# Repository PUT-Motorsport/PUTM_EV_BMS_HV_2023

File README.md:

# PUTM_EV_BMS_HV_MASTER_2023
Accumulator Managment System (High Voltage Battery Managment System)

## Overview
The AMS system consists of two main parts, the master and multiple slaves.

The apparatus is responsible for the managment of the battery as a whole, determining it's states like: state of charge or unsafe state plausibility. It also supervises the turning on and off of the hv bus.

## Master
The AMS Master is the center of the whole system it's responsible for most of the tasks: current measurement, high voltage relay control, slave control, high voltage measurement and communication with the car. 

### Software
The AMS system havely relies on RTOS (Real Time Operating System) for seperating and managing different tasks. The system is divided mainly into three parts:
- main task - responsible for control over the whole system,
- subsidiary tasks - for off handling time consuming calculations or interfacing,
- communication tasks - for handling communication with external systems like CAN communication with the car or isoSPI for communication with the slaves.

### Hardware 
The AMS is powered by STM32G484xx, a powerful, new gen MCU capable of handling varius communication interfaces and tasks. On board there are also three 24bit ADC ICs responsible for taking precise measurments of flowing current and voltage present on HV bus. For interfacing with other components the AMS uses M80 and M300 series Harwin connectors which offer high reliability. The board also features other logic components all on a custom 4 layer board.

### The research and development work was carried out was a part of the Student Scientific Clubs Create Innovations (SKNTI) program. [Ministry of Science and Higher Education](https://www.gov.pl/web/nauka)

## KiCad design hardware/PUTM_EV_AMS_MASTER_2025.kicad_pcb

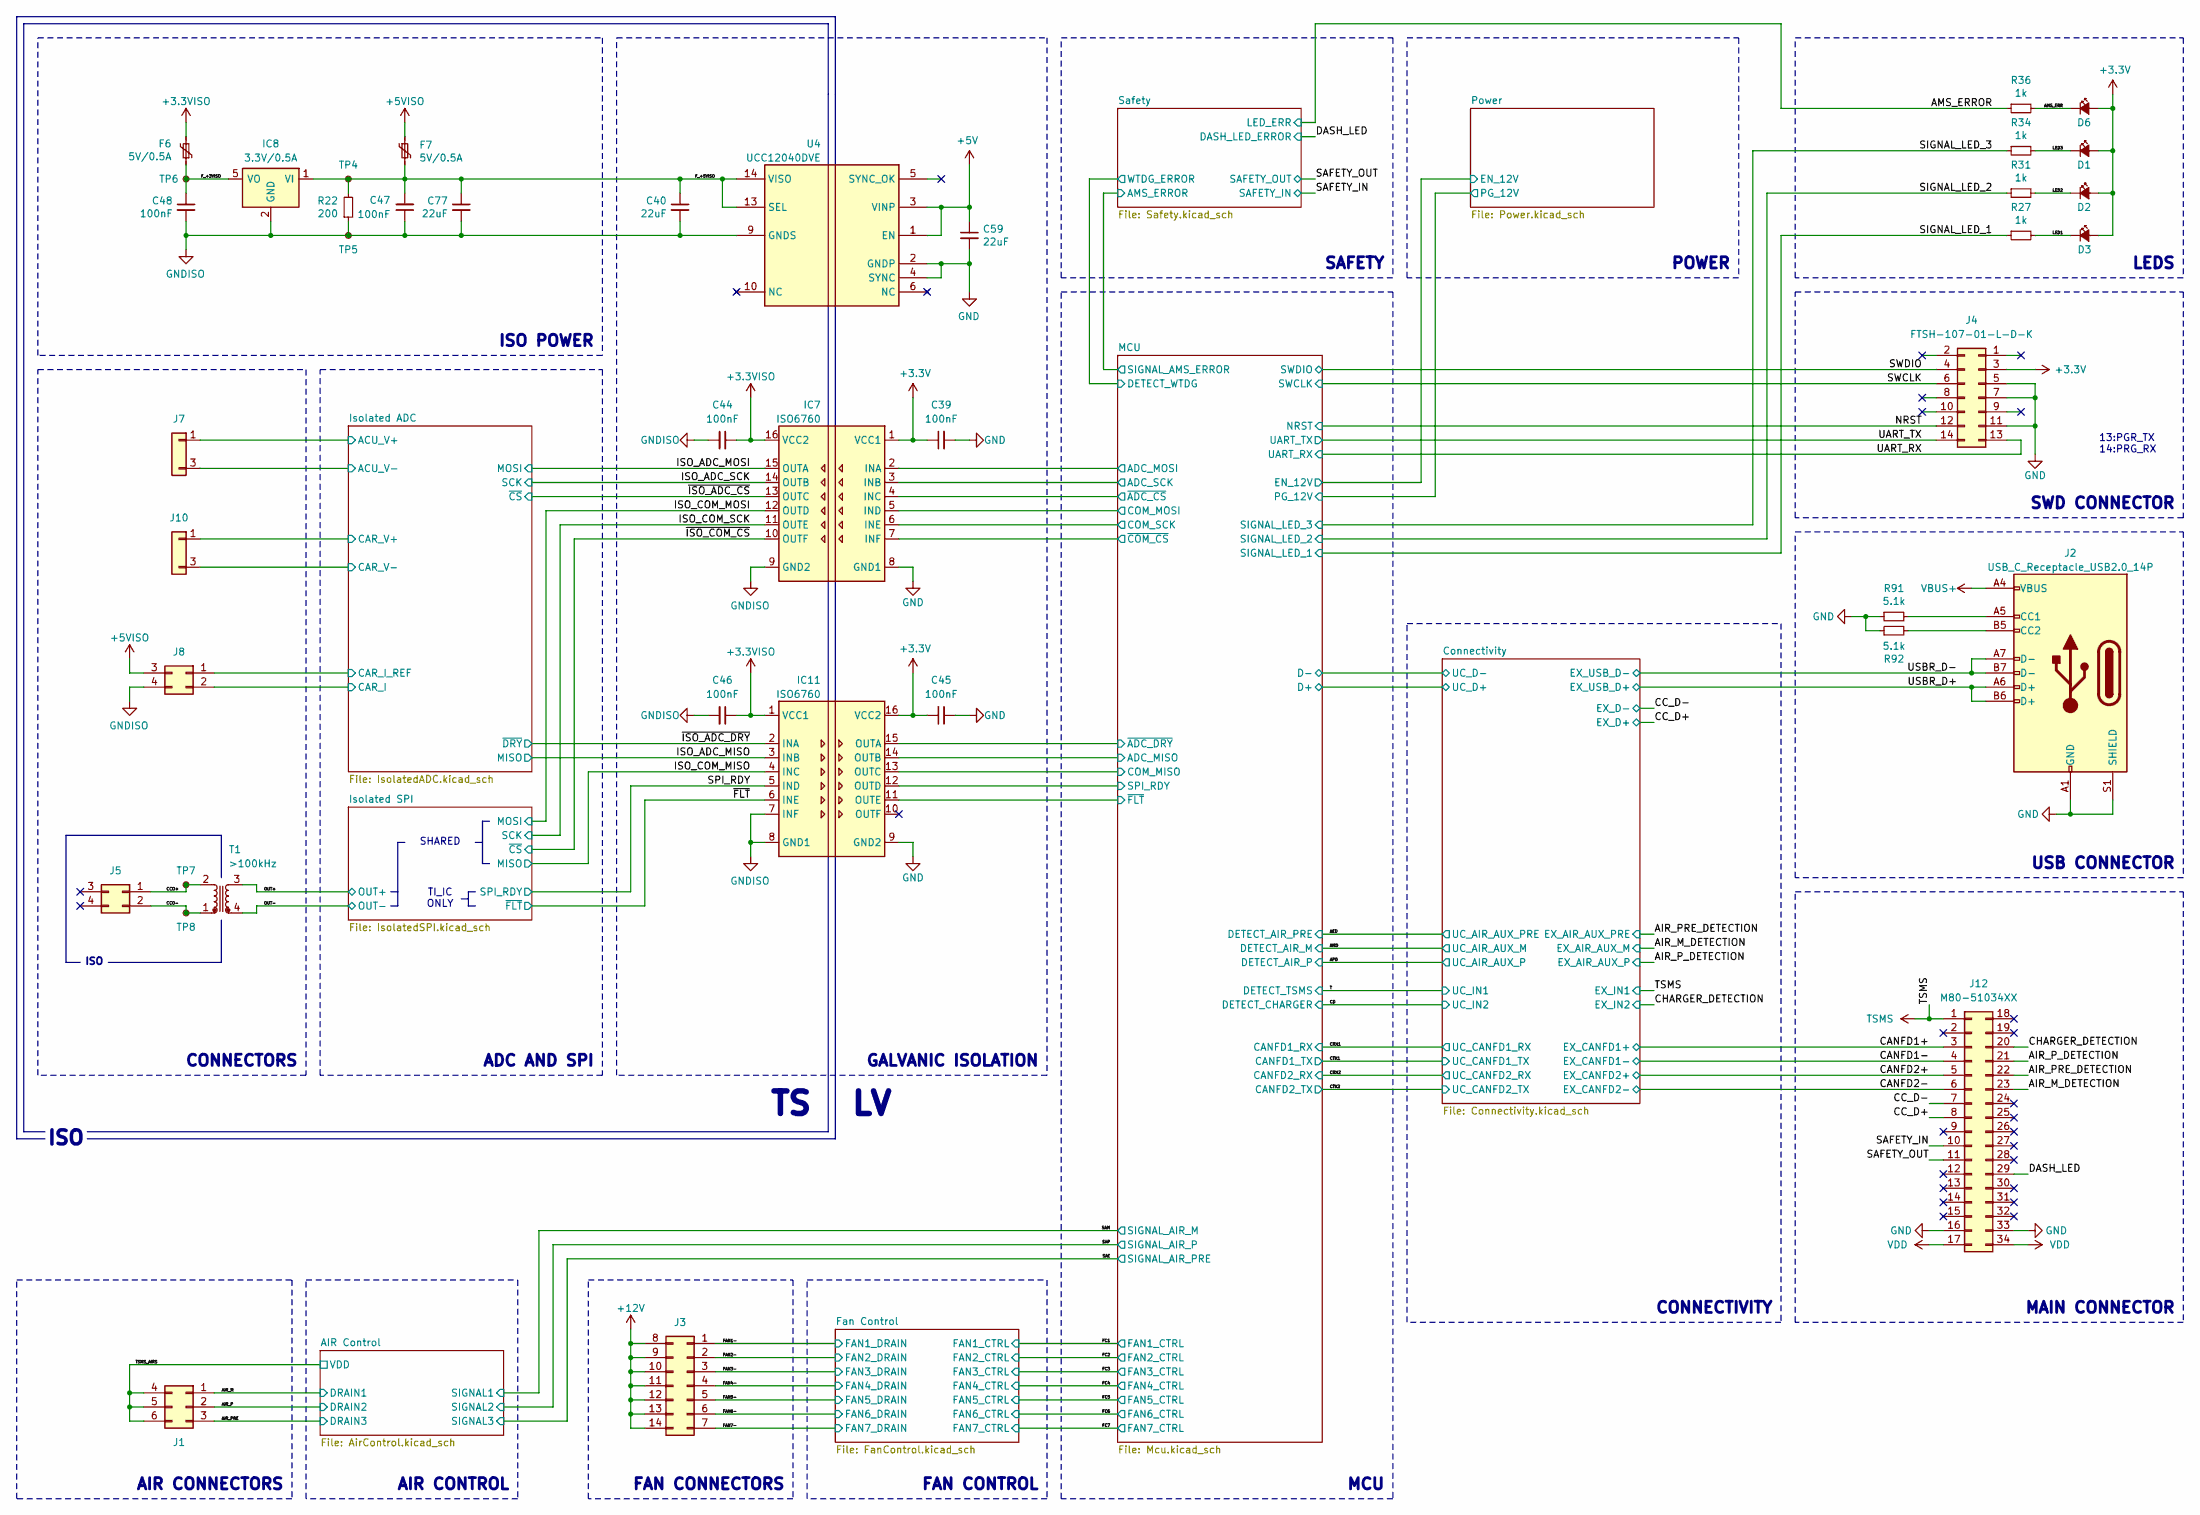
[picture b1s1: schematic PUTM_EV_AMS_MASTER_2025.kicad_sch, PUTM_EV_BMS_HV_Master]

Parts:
C39, C44, C45, C46, C47, C48: 100nF; C_0603_1608Metric; Manufacturer_Part_Number --
C40, C59, C77: 22uF; C_0805_2012Metric; Manufacturer_Part_Number --
D1, D2, D3, D6: SML-D12U1WT86; LED_0603_1608Metric; Manufacturer_Part_Number --
F6, F7: 5V/0.5A; Fuse_0805_2012Metric; Manufacturer_Part_Number 0ZCH0050FF2G; Mouser Part Number 530-0ZCH0050FF2G
IC7, IC11: ISO6760; SOIC-16W_7.5x10.3mm_P1.27mm; Mouser Part Number 595-ISO6760QDWRQ1
IC8: 3.3V/0.5A; SOT-23-5; Mouser Part Number 595-TPS7B92033DBVR
J1: M80-5100642; M80-51006YY; Mouser Part Number 855-M80-5100642
J2: USB_C_Receptacle_USB2.0_14P; USB_C_Receptacle_JAE_DX07S024WJ3R400
J3: M80-51014XX; M80-51014YY; Mouser Part Number 855-M80-5101422
J4: FTSH-107-01-L-D-K; FTSH-107-XX-YYY-D-K; Mouser Part Number 200-FTSH10701LDK
J5, J8: M80-51004XX; M80-51004YY; Mouser Part Number 855-M80-5100442
J7, J10: M300-MV10345M1; M300MV10345M1; Mouser Part Number 855-M300-MV10345M1
J12: M80-51034XX; M80-51034YY; Mouser Part Number 855-M80-5103442
R22: 200; R_0603_1608Metric; Manufacturer_Part_Number --
R27, R31, R34, R36: 1k; R_0603_1608Metric; Manufacturer_Part_Number --
R91, R92: 5.1k; R_0603_1608Metric; Manufacturer_Part_Number --
T1: >100kHz; SOP254P914X350-4N; Mouser Part Number 851-ESMIT-4180/C
TP4, TP5, TP6, TP7, TP8: TestPoint_Small; TestPoint_THTPad_D1.0mm_Drill0.5mm
U4: UCC12040DVE; SOIC-16W_7.5x10.3mm_P1.27mm; Mouser Part Number 595-UCC12040DVE

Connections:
+3.3V: C39.1, C45.1, D1.2 (A), D2.2 (A), D3.2 (A), D6.2 (A), IC7.1 (VCC1), IC11.16 (VCC2), J4.3; also elsewhere on the board
+3.3VISO: C44.1, C46.1, F6.2, IC7.16 (VCC2), IC11.1 (VCC1); also elsewhere on the board
+5V: C59.1, U4.1 (EN), U4.3 (VINP); also elsewhere on the board
+5VISO: F7.1, J8.3; also elsewhere on the board
+12V: J3.8, J3.9, J3.10, J3.11, J3.12, J3.13, J3.14; also elsewhere on the board
/AIR_M: J1.1; also elsewhere on the board
/AIR_M_DETECTION: J12.23; also elsewhere on the board
/AIR_P: J1.2; also elsewhere on the board
/AIR_PRE: J1.3; also elsewhere on the board
/AIR_PRE_DETECTION: J12.22; also elsewhere on the board
/AIR_P_DETECTION: J12.21; also elsewhere on the board
/AMS_ERR: D6.1 (K), R36.2
/AMS_ERROR: R36.1; also elsewhere on the board
/CANFD1+: J12.3; also elsewhere on the board
/CANFD1-: J12.4; also elsewhere on the board
/CANFD2+: J12.5; also elsewhere on the board
/CANFD2-: J12.6; also elsewhere on the board
/CCO+: J5.1, T1.2, TP7.1
/CCO-: J5.2, T1.1, TP8.1
/CC_D+: J12.8; also elsewhere on the board
/CC_D-: J12.7; also elsewhere on the board
/CHARGER_DETECTION: J12.20; also elsewhere on the board
/DASH_LED: J12.29; also elsewhere on the board
/FAN1-: J3.1; also elsewhere on the board
/FAN2-: J3.2; also elsewhere on the board
/FAN3-: J3.3; also elsewhere on the board
/FAN4-: J3.4; also elsewhere on the board
/FAN5-: J3.5; also elsewhere on the board
/FAN6-: J3.6; also elsewhere on the board
/FAN7-: J3.7; also elsewhere on the board
/F_+3VISO: C48.1, F6.1, IC8.5 (VO), TP6.1
/F_+5VISO: C40.1, C47.2, C77.1, F7.2, IC8.1 (VI), R22.2, TP4.1, U4.13 (SEL), U4.14 (VISO)
/ISO_ADC_MISO: IC11.3 (INB); also elsewhere on the board
/ISO_ADC_MOSI: IC7.15 (OUTA); also elsewhere on the board
/ISO_ADC_SCK: IC7.14 (OUTB); also elsewhere on the board
/ISO_COM_MISO: IC11.4 (INC); also elsewhere on the board
/ISO_COM_MOSI: IC7.12 (OUTD); also elsewhere on the board
/ISO_COM_SCK: IC7.11 (OUTE); also elsewhere on the board
/Isolated ADC/ACU_V+: J7.1; also elsewhere on the board
/Isolated ADC/ACU_V-: J7.3; also elsewhere on the board
/Isolated ADC/CAR_V+: J10.1; also elsewhere on the board
/Isolated ADC/CAR_V-: J10.3; also elsewhere on the board
/Isolated ADC/I+: J8.2; also elsewhere on the board
/Isolated ADC/I-: J8.1; also elsewhere on the board
/LED1: D3.1 (K), R27.2
/LED2: D2.1 (K), R31.2
/LED3: D1.1 (K), R34.2
/MCU/ADC_MISO: IC11.14 (OUTB); also elsewhere on the board
/MCU/ADC_MOSI: IC7.2 (INA); also elsewhere on the board
/MCU/ADC_SCK: IC7.3 (INB); also elsewhere on the board
/MCU/COM_MISO: IC11.13 (OUTC); also elsewhere on the board
/MCU/COM_MOSI: IC7.5 (IND); also elsewhere on the board
/MCU/COM_SCK: IC7.6 (INE); also elsewhere on the board
/MCU/SPI_RDY: IC11.12 (OUTD); also elsewhere on the board
/MCU/~ADC_CS: IC7.4 (INC); also elsewhere on the board
/MCU/~ADC_DRY: IC11.15 (OUTA); also elsewhere on the board
/MCU/~COM_CS: IC7.7 (INF); also elsewhere on the board
/MCU/~FLT: IC11.11 (OUTE); also elsewhere on the board
/NRST: J4.12; also elsewhere on the board
/OUT+: T1.3; also elsewhere on the board
/OUT-: T1.4; also elsewhere on the board
/SAFETY_IN: J12.10; also elsewhere on the board
/SAFETY_OUT: J12.11; also elsewhere on the board
/SIGNAL_LED_1: R27.1; also elsewhere on the board
/SIGNAL_LED_2: R31.1; also elsewhere on the board
/SIGNAL_LED_3: R34.1; also elsewhere on the board
/SPI_RDY: IC11.5 (IND); also elsewhere on the board
/SWCLK: J4.6; also elsewhere on the board
/SWDIO: J4.4; also elsewhere on the board
/TSMS_AIRS: J1.4, J1.5, J1.6; also elsewhere on the board
/UART_RX: J4.13; also elsewhere on the board
/UART_TX: J4.14; also elsewhere on the board
/USBR_D+: J2.A6 (D+), J2.B6 (D+); also elsewhere on the board
/USBR_D-: J2.A7 (D-), J2.B7 (D-); also elsewhere on the board
/~FLT: IC11.6 (INE); also elsewhere on the board
/~ISO_ADC_CS: IC7.13 (OUTC); also elsewhere on the board
/~ISO_ADC_DRY: IC11.2 (INA); also elsewhere on the board
/~ISO_COM_CS: IC7.10 (OUTF); also elsewhere on the board
GND: C39.2, C45.2, C59.2, IC7.8 (GND1), IC11.9 (GND2), J2.A1 (GND), J2.A12 (GND), J2.B1 (GND), J2.B12 (GND), J2.S1 (SHIELD), J4.5, J4.7, J4.11, J12.16, J12.33, R91.1, R92.1, U4.2 (GNDP), U4.4 (SYNC); also elsewhere on the board
GNDISO: C40.2, C44.2, C46.2, C47.1, C48.2, C77.2, IC7.9 (GND2), IC8.2 (GND), IC11.7 (INF), IC11.8 (GND1), J8.4, R22.1, TP5.1, U4.9 (GNDS), U4.15 (GNDS), U4.16 (GNDS); also elsewhere on the board
unnamed: J2.A5 (CC1), R91.2
unnamed: J2.B5 (CC2), R92.2
TSMS: J12.1; also elsewhere on the board
VBUS+: J2.A4 (VBUS), J2.A9 (VBUS), J2.B4 (VBUS), J2.B9 (VBUS); also elsewhere on the board
VDD: J12.17, J12.34; also elsewhere on the board

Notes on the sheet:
TI_IC ONLY
GALVANIC ISOLATION
FAN CONNECTORS
MAIN CONNECTOR
SAFETY
MCU
AIR CONNECTORS
SHARED
FAN CONTROL
LEDS
SWD CONNECTOR
USB CONNECTOR
13:PGR_TX 14:PRG_RX
ISO
AIR CONTROL
CONNECTORS
CONNECTIVITY
ISO POWER
POWER
ADC AND SPI

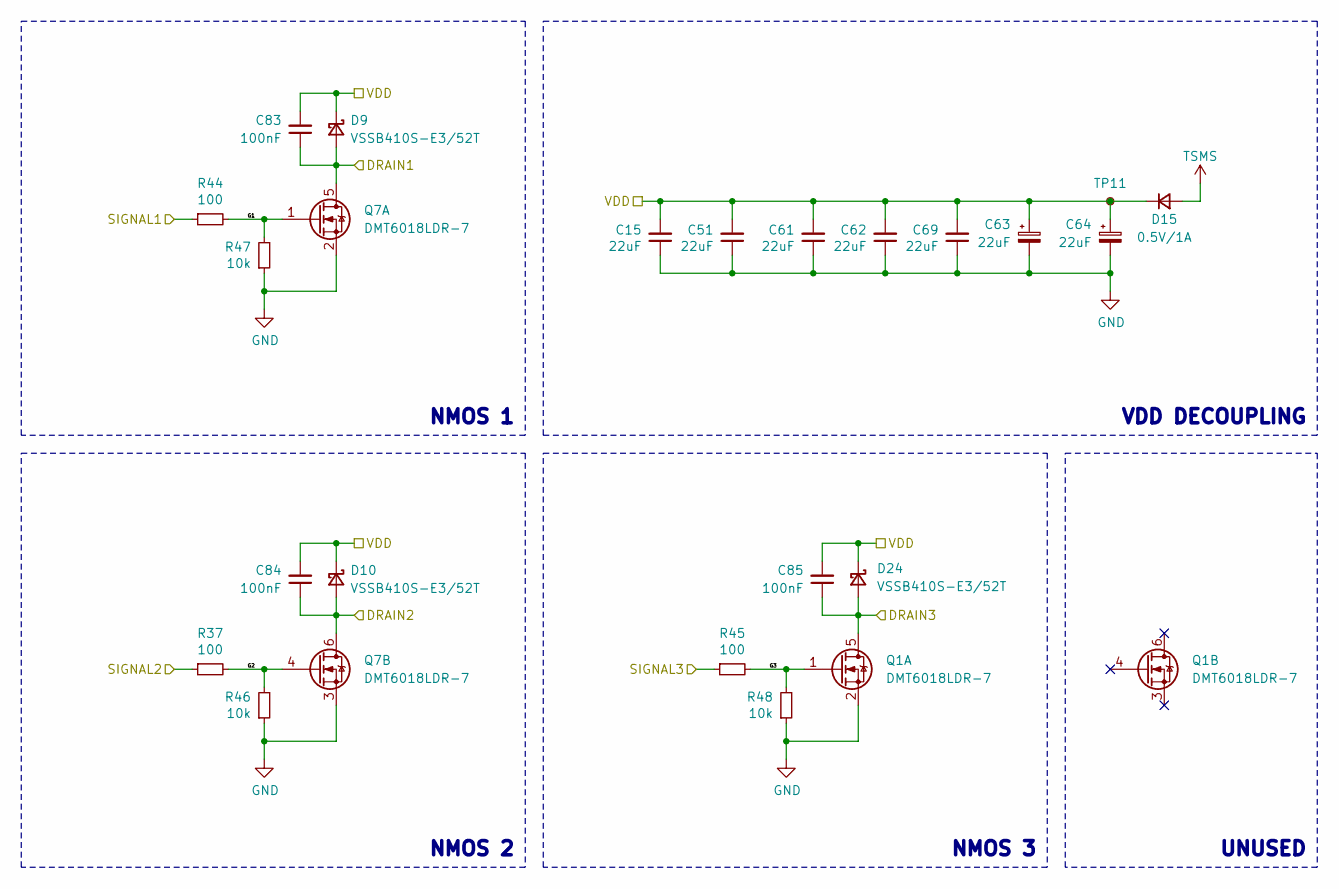
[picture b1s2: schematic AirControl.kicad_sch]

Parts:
C15, C51, C61, C62, C69: 22uF; C_0805_2012Metric; Manufacturer_Part_Number CL21A107MQYNNWE
C63, C64: 22uF; CP_Elec_4x5.8
C83, C84, C85: 100nF; C_0603_1608Metric; Manufacturer_Part_Number --
D9, D10, D24: VSSB410S-E3/52T; D_SOD-123; Manufacturer_Part_Number VSSB410S-E3/52T; Mouser Part Number 625-VSSB410S-E3/52T
D15: 0.5V/1A; D_SOD-123
Q1, Q7: DMT6018LDR-7; DMT6018LDR7; Mouser Part Number 621-DMT6018LDR-7
R37, R44, R45: 100; R_0603_1608Metric; Manufacturer_Part_Number --
R46, R47, R48: 10k; R_0603_1608Metric; Manufacturer_Part_Number --
TP11: TestPoint_Small; TestPoint_THTPad_D1.0mm_Drill0.5mm

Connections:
/AIR Control/G1: Q7.1 (G1), R44.2, R47.2
/AIR Control/G2: Q7.4 (G2), R37.2, R46.2
/AIR Control/G3: Q1.1 (G1), R45.2, R48.2
/AIR_M: C83.1, D9.2 (A), Q7.5 (D1); also elsewhere on the board
/AIR_P: C84.1, D10.2 (A), Q7.6 (D2); also elsewhere on the board
/AIR_PRE: C85.1, D24.2 (A), Q1.5 (D1); also elsewhere on the board
/SAE: R45.1; also elsewhere on the board
/SAM: R44.1; also elsewhere on the board
/SAP: R37.1; also elsewhere on the board
/TSMS_AIRS: C15.2, C51.2, C61.2, C62.2, C63.1, C64.1, C69.2, C83.2, C84.2, C85.2, D9.1 (K), D10.1 (K), D15.1 (K), D24.1 (K), TP11.1; also elsewhere on the board
GND: C15.1, C51.1, C61.1, C62.1, C63.2, C64.2, C69.1, Q1.2 (S1), Q7.2 (S1), Q7.3 (S2), R46.1, R47.1, R48.1; also elsewhere on the board
TSMS: D15.2 (A); also elsewhere on the board

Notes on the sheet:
UNUSED
NMOS 1
VDD DECOUPLING
NMOS 2
NMOS 3

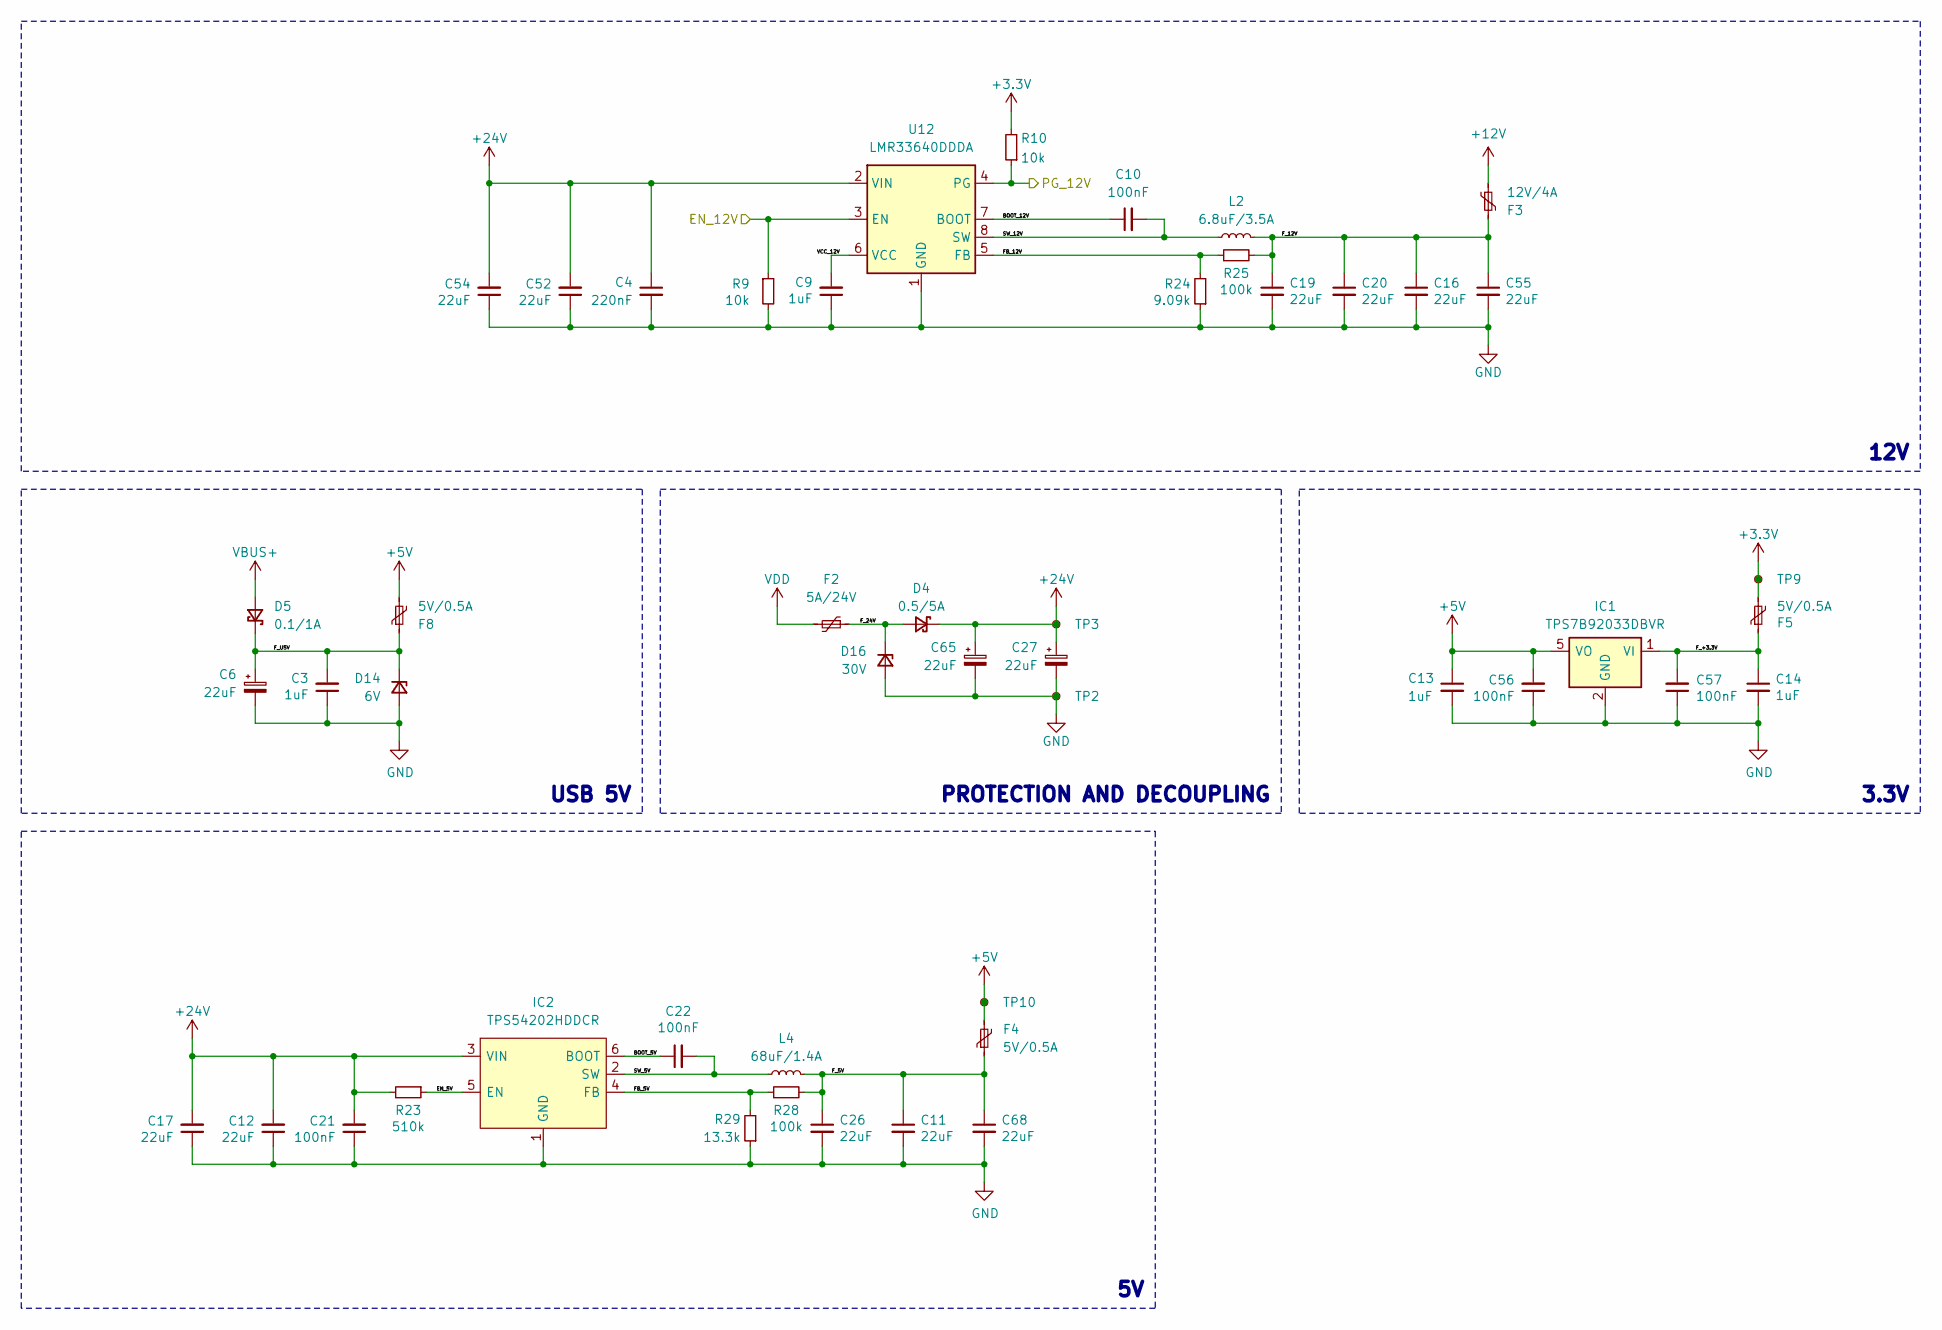
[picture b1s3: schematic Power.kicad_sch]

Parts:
C3, C9: 1uF; C_0603_1608Metric; Manufacturer_Part_Number C0603C104J3RACTU
C4: 220nF; C_0603_1608Metric; Manufacturer_Part_Number --
C6, C27, C65: 22uF; CP_Elec_4x5.8
C10, C21, C22, C56, C57: 100nF; C_0603_1608Metric; Manufacturer_Part_Number C0603C104J3RACTU
C11, C12, C16, C17, C19, C20, C26, C52, C54, C55, C68: 22uF; C_0805_2012Metric; Manufacturer_Part_Number CL21A107MQYNNWE
C13, C14: 1uF; C_0603_1608Metric; Manufacturer_Part_Number C0603C105K8RACTU
D4: 0.5/5A; D_SOD-123
D5: 0.1/1A; D_SOD-123
D14: 6V; D_SOD-123
D16: 30V; D_SOD-123
F2: 5A/24V; Fuse_2920_7451Metric; Mouser Part Number 576-2920L500/24SLDR
F3: 12V/4A; Fuse_1206_3216Metric; Manufacturer_Part_Number 1206L400/12SLWR; Mouser Part Number 576-1206L400/12SLWR
F4, F5, F8: 5V/0.5A; Fuse_0805_2012Metric; Manufacturer_Part_Number 0ZCH0050FF2G; Mouser Part Number 530-0ZCH0050FF2G
IC1: TPS7B92033DBVR; SOT-23-5; Mouser Part Number 595-TPS7B92033DBVR
IC2: TPS54202HDDCR; SOT-23-6; Mouser Part Number 595-TPS54202HDDCR
L2: 6.8uF/3.5A; L_TDK_VLS6045EX_VLS6045AF; Mouser Part Number 810-VLS6045AF-6R8M
L4: 68uF/1.4A; L_TDK_VLS6045EX_VLS6045AF; Mouser Part Number 810-VLS6045EX-680M
R9, R10: 10k; R_0603_1608Metric; Manufacturer_Part_Number RT0603DRE07100KL
R23: 510k; R_0603_1608Metric; Manufacturer_Part_Number RT0603DRD07510KL; Mouser Part Number 603-RT0603DRD07510KL
R24: 9.09k; R_0603_1608Metric; Manufacturer_Part_Number RT0603DRE0713K3L; Mouser Part Number 603-RT0603DRE0713K3L
R25, R28: 100k; R_0603_1608Metric; Manufacturer_Part_Number RT0603DRE07100KL
R29: 13.3k; R_0603_1608Metric; Manufacturer_Part_Number RT0603DRE0713K3L; Mouser Part Number 603-RT0603DRE0713K3L
TP2: TestPoint_Small; MountingHole_3.2mm_M3_Pad_Via
TP3, TP9, TP10: TestPoint_Small; TestPoint_THTPad_D1.0mm_Drill0.5mm
U12: LMR33640DDDA; Texas_HSOP-8-1EP_3.9x4.9mm_P1.27mm; Mouser Part Number LMR33640DDDAR

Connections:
+3.3V: F5.2, R10.2, TP9.1; also elsewhere on the board
+5V: C13.1, C56.2, F4.2, F8.2, IC1.5 (VO), TP10.1; also elsewhere on the board
+12V: F3.1; also elsewhere on the board
+24V: C4.1, C12.2, C17.2, C21.2, C27.1, C52.2, C54.2, C65.1, D4.1 (K), IC2.3 (VIN), R23.2, TP3.1, U12.2 (VIN); also elsewhere on the board
/MCU/EN_12V: R9.1, U12.3 (EN); also elsewhere on the board
/MCU/PG_12V: R10.1, U12.4 (PG); also elsewhere on the board
/Power/BOOT_5V: C22.1, IC2.6 (BOOT)
/Power/BOOT_12V: C10.1, U12.7 (BOOT)
/Power/EN_5V: IC2.5 (EN), R23.1
/Power/FB_5V: IC2.4 (FB), R28.1, R29.2
/Power/FB_12V: R24.2, R25.1, U12.5 (FB)
/Power/F_5V: C11.1, C26.1, C68.1, F4.1, L4.2, R28.2
/Power/F_12V: C16.1, C19.1, C20.1, C55.1, F3.2, L2.2, R25.2
/Power/F_24V: D4.2 (A), D16.1 (K), F2.1
/Power/F_+3.3V: C14.1, C57.2, F5.1, IC1.1 (VI)
/Power/F_U5V: C3.2, C6.1, D5.1 (K), D14.1 (K), F8.1
/Power/SW_5V: C22.2, IC2.2 (SW), L4.1
/Power/SW_12V: C10.2, L2.1, U12.8 (SW)
/Power/VCC_12V: C9.2, U12.6 (VCC)
GND: C3.1, C4.2, C6.2, C9.1, C11.2, C12.1, C13.2, C14.2, C16.2, C17.1, C19.2, C20.2, C21.1, C26.2, C27.2, C52.1, C54.1, C55.2, C56.1, C57.1, C65.2, C68.2, D14.2 (A), D16.2 (A), IC1.2 (GND), IC2.1 (GND), R9.2, R24.1, R29.1, TP2.1, U12.1 (GND), U12.9 (GND); also elsewhere on the board
VBUS+: D5.2 (A); also elsewhere on the board
VDD: F2.2; also elsewhere on the board

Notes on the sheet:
PROTECTION AND DECOUPLING
3.3V
12V
USB 5V

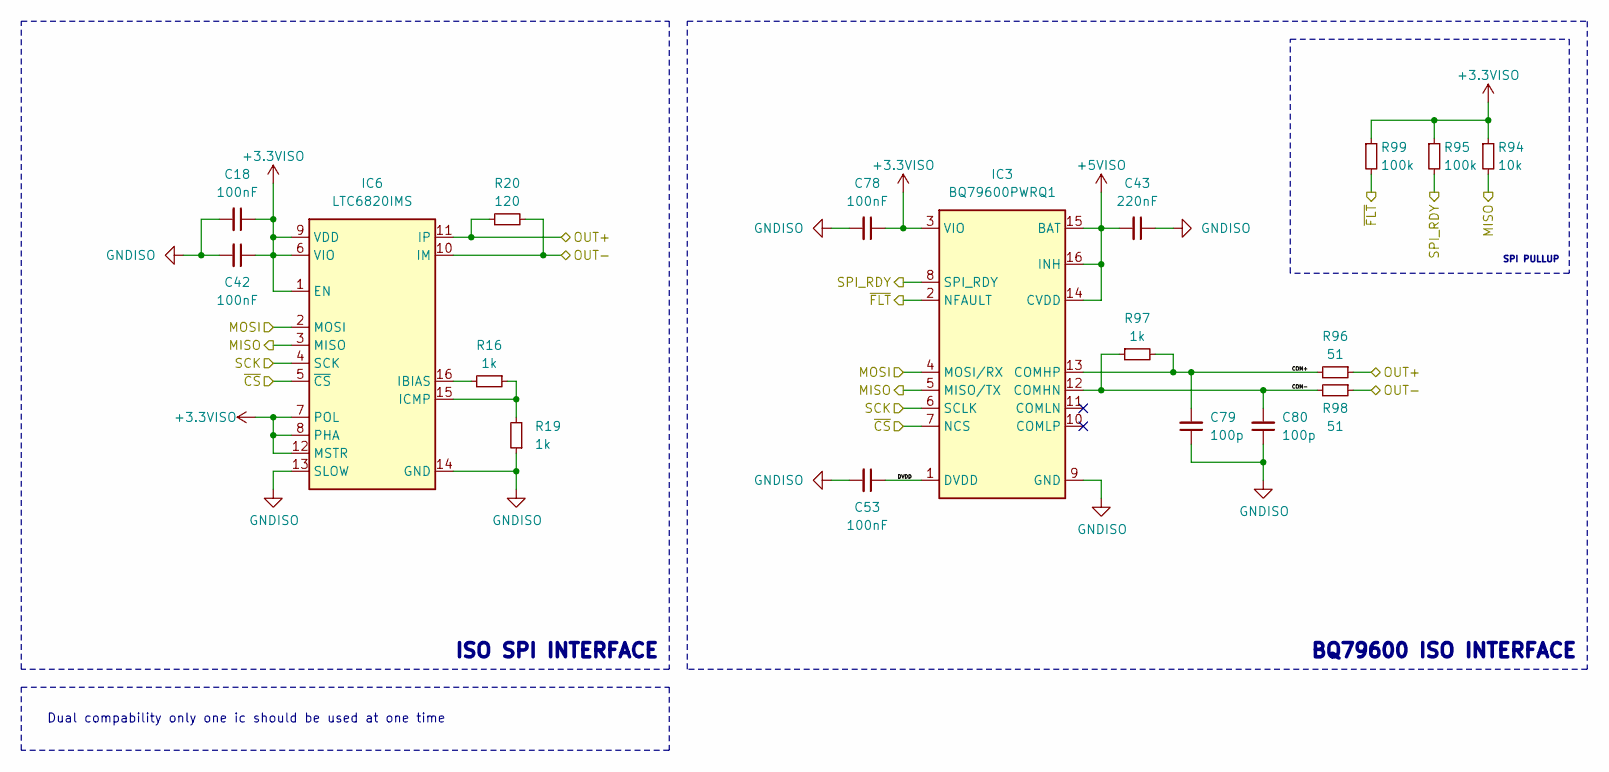
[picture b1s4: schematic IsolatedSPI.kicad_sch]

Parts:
C18, C42, C53, C78: 100nF; C_0603_1608Metric; Manufacturer_Part_Number --
C43: 220nF; C_0603_1608Metric; Manufacturer_Part_Number --
C79, C80: 100p; C_0603_1608Metric; Manufacturer_Part_Number --
IC3: BQ79600PWRQ1; TSSOP-16_4.4x5mm_P0.65mm; Mouser Part Number 595-BQ79600PWRQ1
IC6: LTC6820IMS; MSOP-16_3x4.039mm_P0.5mm; Mouser Part Number LTC6820IMS#PBF
R16, R19, R97: 1k; R_0603_1608Metric; Manufacturer_Part_Number --
R20: 120; R_0603_1608Metric; Manufacturer_Part_Number --
R94: 10k; R_0603_1608Metric; Manufacturer_Part_Number --
R95, R99: 100k; R_0603_1608Metric; Manufacturer_Part_Number --
R96, R98: 51; R_0603_1608Metric; Manufacturer_Part_Number --

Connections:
+3.3VISO: C18.1, C42.1, C78.1, IC3.3 (VIO), IC6.1 (EN), IC6.6 (VIO), IC6.7 (POL), IC6.8 (PHA), IC6.9 (VDD), IC6.12 (MSTR), R94.1, R95.1, R99.1; also elsewhere on the board
+5VISO: C43.2, IC3.14 (CVDD), IC3.15 (BAT), IC3.16 (INH); also elsewhere on the board
/ISO_COM_MISO: IC3.5 (MISO/TX), IC6.3 (MISO), R94.2; also elsewhere on the board
/ISO_COM_MOSI: IC3.4 (MOSI/RX), IC6.2 (MOSI); also elsewhere on the board
/ISO_COM_SCK: IC3.6 (SCLK), IC6.4 (SCK); also elsewhere on the board
/Isolated SPI/COM+: C79.2, IC3.13 (COMHP), R96.2, R97.2
/Isolated SPI/COM-: C80.2, IC3.12 (COMHN), R97.1, R98.2
/Isolated SPI/DVDD: C53.1, IC3.1 (DVDD)
/OUT+: IC6.11 (IP), R20.1, R96.1; also elsewhere on the board
/OUT-: IC6.10 (IM), R20.2, R98.1; also elsewhere on the board
/SPI_RDY: IC3.8 (SPI_RDY), R95.2; also elsewhere on the board
/~FLT: IC3.2 (NFAULT), R99.2; also elsewhere on the board
/~ISO_COM_CS: IC3.7 (NCS), IC6.5 (~CS); also elsewhere on the board
GNDISO: C18.2, C42.2, C43.1, C53.2, C78.2, C79.1, C80.1, IC3.9 (GND), IC6.13 (SLOW), IC6.14 (GND), R19.1; also elsewhere on the board
unnamed: IC6.16 (IBIAS), R16.2
unnamed: IC6.15 (ICMP), R16.1, R19.2

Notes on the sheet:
Dual compability only one ic should be used at one time
ISO SPI INTERFACE
SPI PULLUP
BQ79600 ISO INTERFACE

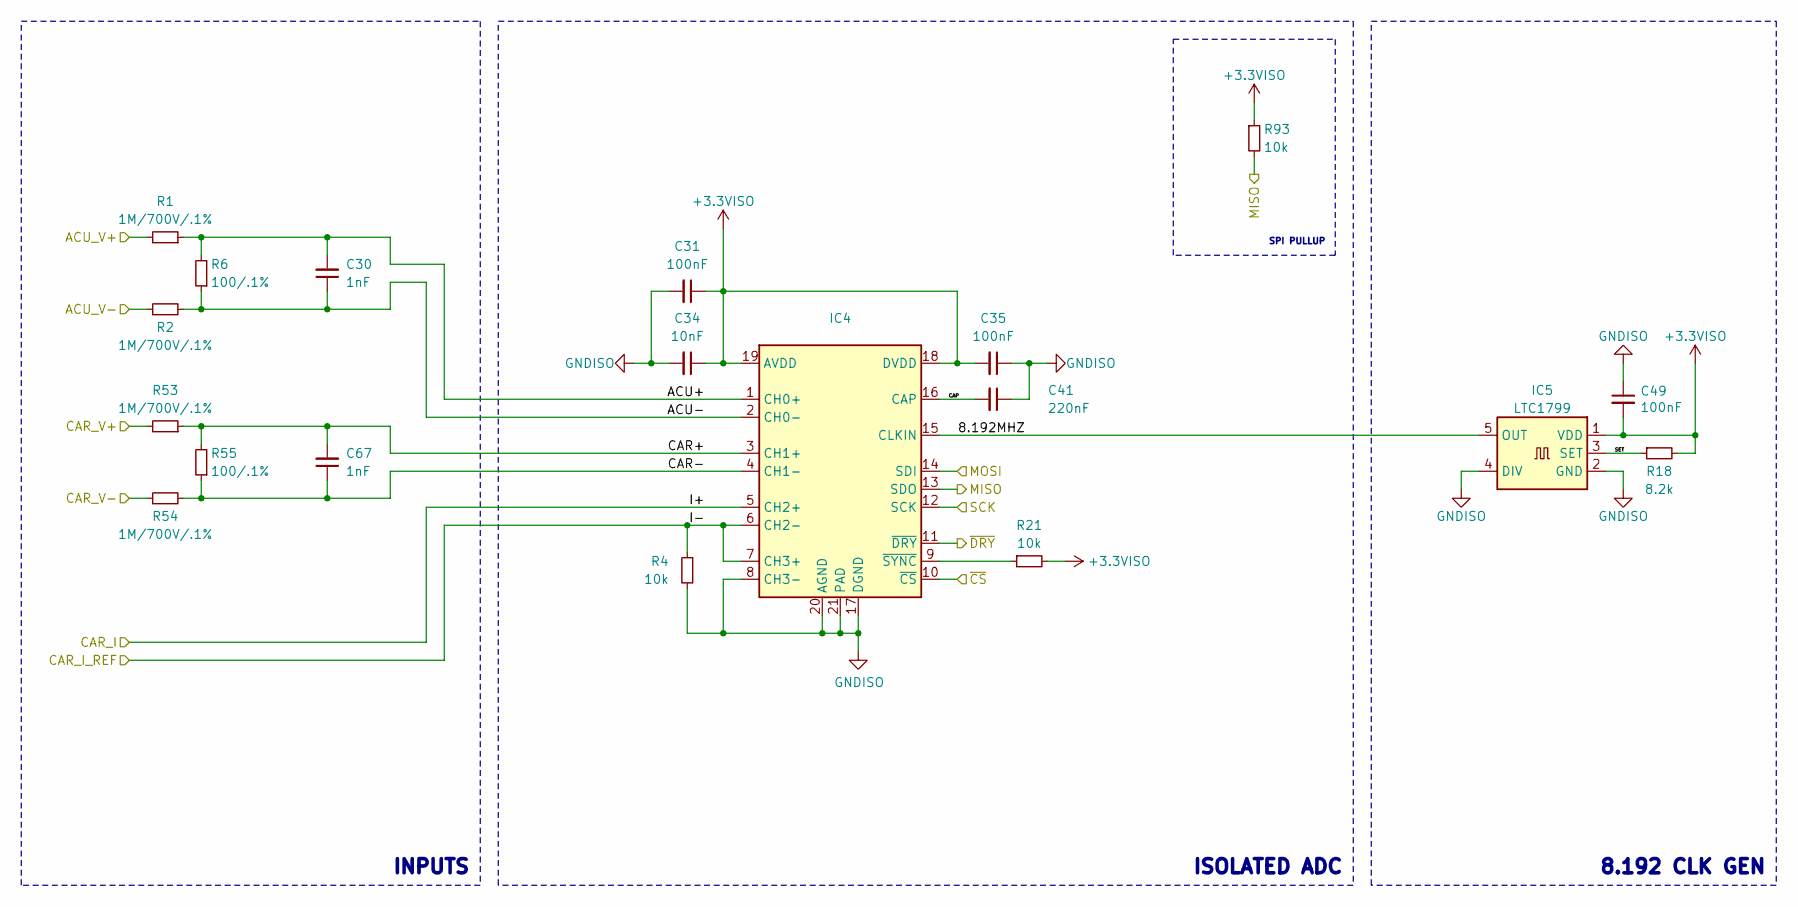
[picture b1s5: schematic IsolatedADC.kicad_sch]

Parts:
C30, C67: 1nF; C_0603_1608Metric; Manufacturer_Part_Number --
C31, C35, C49: 100nF; C_0603_1608Metric; Manufacturer_Part_Number --
C34: 10nF; C_0603_1608Metric; Manufacturer_Part_Number --
C41: 220nF; C_0603_1608Metric; Manufacturer_Part_Number --
IC4: WQFN-20-1EP_3x3mm_P0.4mm_EP1.7x1.7mm; Mouser Part Number ADS131M04IRUKR
IC5: LTC1799; SOT-23-5
R1, R2, R53, R54: 1M/700V/.1%; R_1206_3216Metric; Manufacturer_Part_Number 754-RGV3216P-1004BT1
R4, R21, R93: 10k; R_0603_1608Metric; Manufacturer_Part_Number --
R6, R55: 100/.1%; R_1206_3216Metric; Manufacturer_Part_Number --
R18: 8.2k; R_0603_1608Metric; Manufacturer_Part_Number --

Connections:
+3.3VISO: C31.1, C34.1, C35.2, C49.2, IC4.18 (DVDD), IC4.19 (AVDD), IC5.1 (VDD), R18.2, R21.2, R93.1; also elsewhere on the board
/ISO_ADC_MISO: IC4.13 (SDO), R93.2; also elsewhere on the board
/ISO_ADC_MOSI: IC4.14 (SDI); also elsewhere on the board
/ISO_ADC_SCK: IC4.12 (SCK); also elsewhere on the board
/Isolated ADC/8.192MHZ: IC4.15 (CLKIN), IC5.5 (OUT)
/Isolated ADC/ACU+: C30.2, IC4.1 (CH0+), R1.1, R6.2
/Isolated ADC/ACU-: C30.1, IC4.2 (CH0-), R2.2, R6.1
/Isolated ADC/ACU_V+: R1.2; also elsewhere on the board
/Isolated ADC/ACU_V-: R2.1; also elsewhere on the board
/Isolated ADC/CAP: C41.2, IC4.16 (CAP)
/Isolated ADC/CAR+: C67.2, IC4.3 (CH1+), R53.1, R55.2
/Isolated ADC/CAR-: C67.1, IC4.4 (CH1-), R54.2, R55.1
/Isolated ADC/CAR_V+: R53.2; also elsewhere on the board
/Isolated ADC/CAR_V-: R54.1; also elsewhere on the board
/Isolated ADC/I+: IC4.5 (CH2+); also elsewhere on the board
/Isolated ADC/I-: IC4.6 (CH2-), IC4.7 (CH3+), R4.1; also elsewhere on the board
/Isolated ADC/SET: IC5.3 (SET), R18.1
/~ISO_ADC_CS: IC4.10 (~CS); also elsewhere on the board
/~ISO_ADC_DRY: IC4.11 (~DRY); also elsewhere on the board
GNDISO: C31.2, C34.2, C35.1, C41.1, C49.1, IC4.8 (CH3-), IC4.17 (DGND), IC4.20 (AGND), IC4.21 (PAD), IC5.2 (GND), IC5.4 (DIV), R4.2; also elsewhere on the board
unnamed: IC4.9 (~SYNC), R21.1

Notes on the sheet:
SPI PULLUP
INPUTS
8.192 CLK GEN
ISOLATED ADC

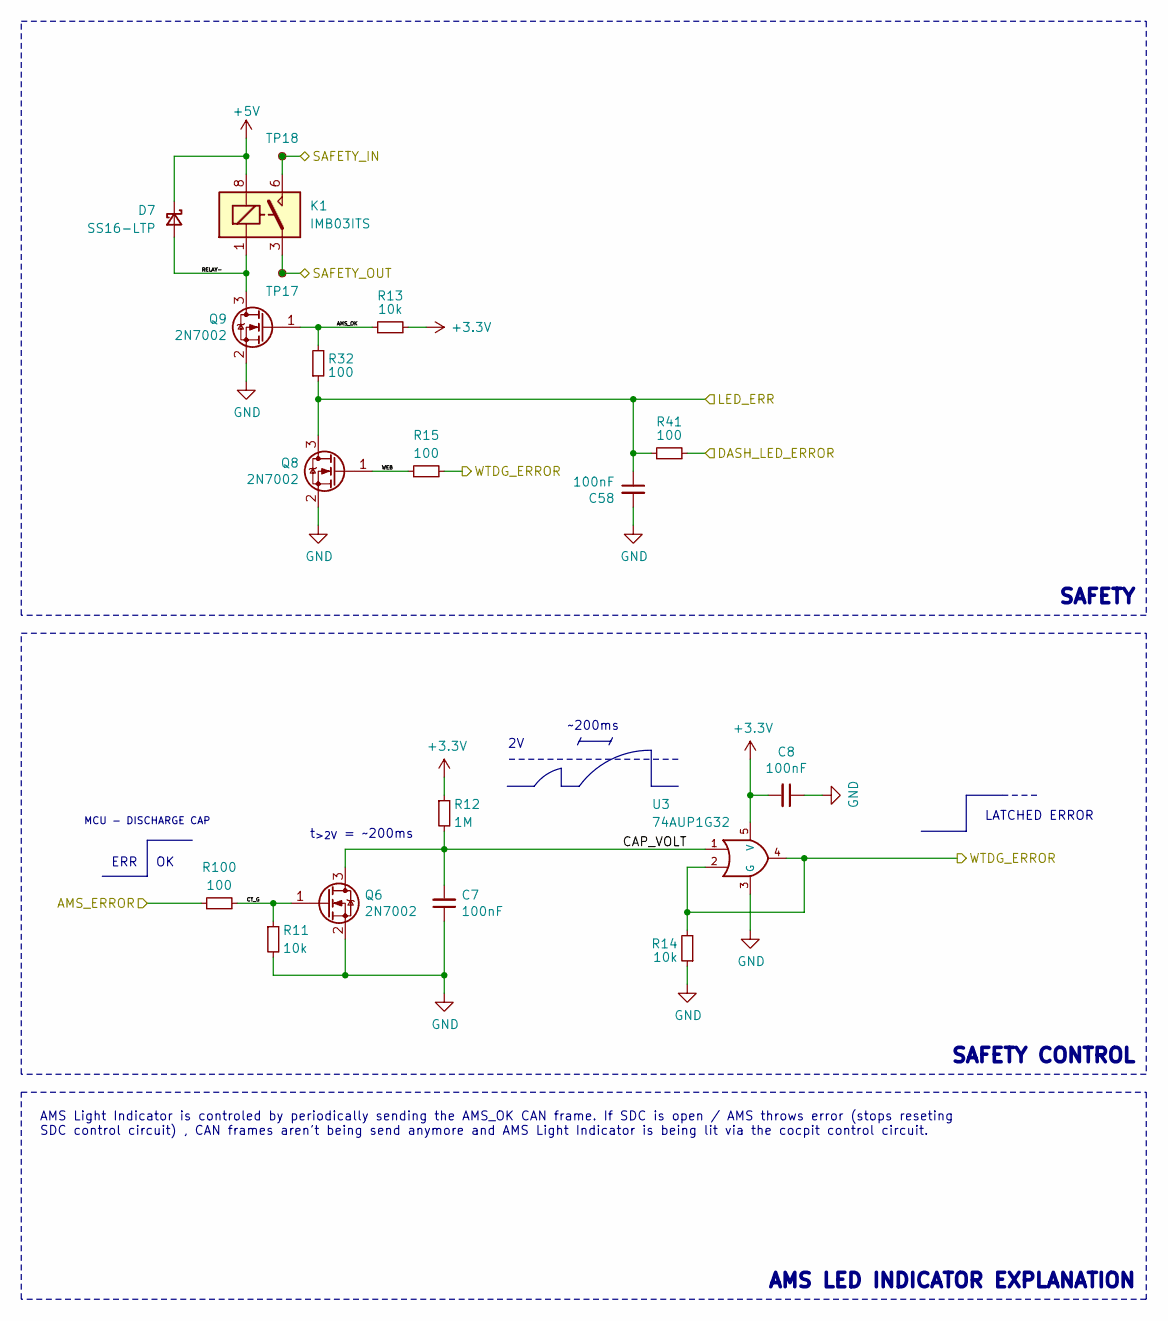
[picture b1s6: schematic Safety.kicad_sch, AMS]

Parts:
C7, C8, C58: 100nF; C_0603_1608Metric; Manufacturer_Part_Number --
D7: SS16-LTP; D_SOD-123; Manufacturer_Part_Number SS16-LTP; Mouser Part Number 833-SS16-LTP
K1: IMB03ITS; Mouser Part Number 655-IMB03ITS
Q6, Q8, Q9: 2N7002; SOT-23; Manufacturer_Part_Number --
R11, R13, R14: 10k; R_0603_1608Metric; Manufacturer_Part_Number --
R12: 1M; R_0603_1608Metric; Manufacturer_Part_Number --
R15, R32, R41, R100: 100; R_0603_1608Metric; Manufacturer_Part_Number --
TP17, TP18: TestPoint_Small; TestPoint_THTPad_D1.0mm_Drill0.5mm
U3: 74AUP1G32; SOT-23-5; Manufacturer_Part_Number SN74AUP1G32DBVR; Mouser Part Number 595-SN74AUP1G32DBVR

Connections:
+3.3V: C8.2, R12.1, R13.2, U3.5 (V); also elsewhere on the board
+5V: D7.1 (K), K1.8 (COIL_2); also elsewhere on the board
/AMS_ERROR: C58.1, Q8.3 (D), R32.1, R41.1; also elsewhere on the board
/DASH_LED: R41.2; also elsewhere on the board
/MCU/DETECT_WTDG: R14.2, R15.2, U3.2, U3.4; also elsewhere on the board
/MCU/SIGNAL_AMS_ERROR: R100.1; also elsewhere on the board
/SAFETY_IN: K1.6 (NO), TP18.1; also elsewhere on the board
/SAFETY_OUT: K1.3 (COM), TP17.1; also elsewhere on the board
/Safety/AMS_OK: Q9.1 (G), R13.1, R32.2
/Safety/CAP_VOLT: C7.2, Q6.3 (D), R12.2, U3.1
/Safety/CT_G: Q6.1 (G), R11.1, R100.2
/Safety/RELAY-: D7.2 (A), K1.1 (COIL_1), Q9.3 (D)
/Safety/WEB: Q8.1 (G), R15.1
GND: C7.1, C8.1, C58.2, Q6.2 (S), Q8.2 (S), Q9.2 (S), R11.2, R14.1, U3.3 (G); also elsewhere on the board

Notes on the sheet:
MCU - DISCHARGE CAP
AMS Light Indicator is controled by periodically sending the AMS_OK CAN frame. If SDC is open / AMS throws error (stops reseting SDC control circuit) , CAN frames aren't being send anymore and AMS Light Indicator is being lit via the cocpit control circuit.
SAFETY CONTROL
~200ms
SAFETY
AMS LED INDICATOR EXPLANATION
ERR
LATCHED ERROR
t_{>2V} = ~200ms
